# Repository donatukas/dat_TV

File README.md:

# dat_TV

* USB based modulator/demodulator with support for EN 300-744 DVB-T
transmission and reception.
* Powered from the USB bus, so no external power adapter is required
Full hardware modulation/demodulation, no host CPU computation required.
* Modulator (Transmitter):
Direct digital conversion to 50~950MHz and 1200~1350 MHz for excellent
signal quality
* UT-100A/UT-100B/UT-100C support configurable bandwidth from 2MHz to 8
MHz.

* Support only non-hierarchy mode
* Programmable digital attenuator
* Free Windows Stream Player
* Free Windows and Linux SDK

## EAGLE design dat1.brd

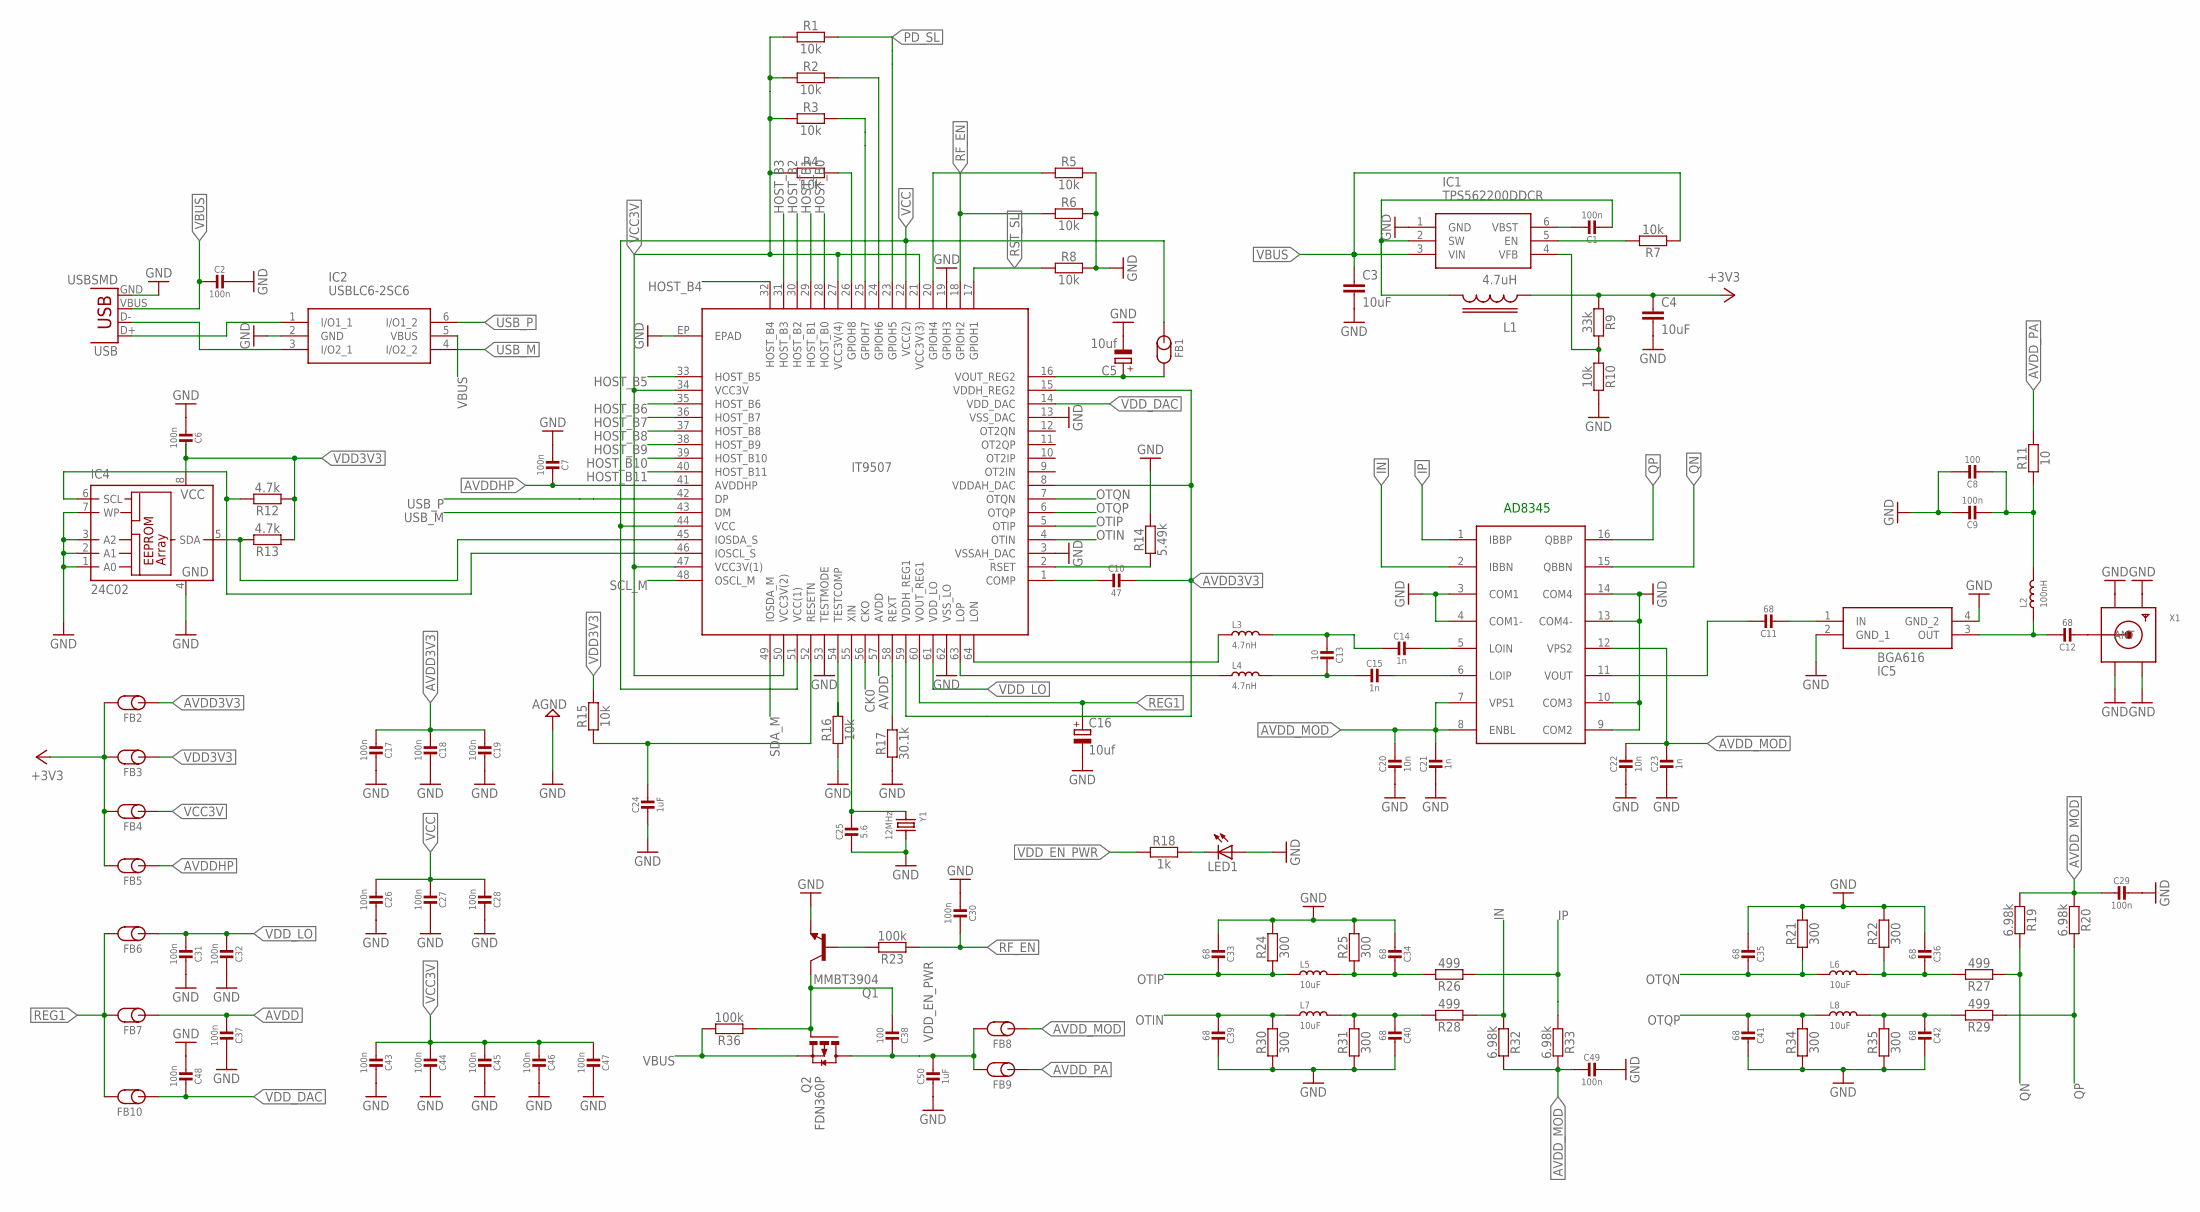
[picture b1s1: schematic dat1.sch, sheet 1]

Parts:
C1, C2, C6, C7, C9, C17, C18, C19, C26, C27, C28, C29, C30, C31, C32, C37, C43, C44, C45, C46, C47, C48, C49: 100n; _0402
C3, C4: 10uF; C0805K
C5, C16: 10uf; SMC_A
C8, C38: 100; _0402
C10: 47; _0402
C11, C12, C33, C34, C35, C36, C39, C40, C41, C42: 68; _0402
C13: 10; _0402
C14, C15, C21, C23: 1n; _0402
C20, C22: 10n; _0402
C24: 1uF; _0402
C25: 5.6; _0402
C50: 1uF; _0603
FB1, FB2, FB3, FB4, FB5, FB6, FB7, FB8, FB9, FB10: FB0603; INDC1608X95N
IC1: TPS562200DDCR; SOT95P280X110-6N
IC2: USBLC6-2SC6; SOT95P280X145-6N
IC3: CRYSTALVIDEO_IT9518; CRYSTALVIDEO_QFN64P40_IT9518
IC4: 24C02; SO-08
IC5: BGA616
IC6: AD8346; QSOP16
L1: 4.7uH; L_3X3
L2: 100nH; L0603@1
L3, L4: 4.7nH; L0603@1
L5, L6, L7, L8: 10uF; L0805@1
LED1: POWER; CHIPLED-0603-TTW
Q1: MMBT3904; SOT23-BEC
Q2: FDN360P; SUPER-SOT3
R1, R2, R3, R4, R5, R6, R7, R8, R10, R15, R16: 10k; C0402
R9: 33k; C0402
R11: 10; C0603
R12, R13: 4.7k; C0402
R14: 5.49k; C0402
R17: 30.1k; C0402
R18: 1k; C0402
R19, R20, R32, R33: 6.98k; C0402
R21, R22, R24, R25, R30, R31, R34, R35: 300; C0402
R23, R36: 100k; C0603
R26, R27, R28, R29: 499; C0402
USB: USBSMD; USB-MINIB
X1: MODULATOR_MICROBUILDER_SMACONNECTOR_EDGE_UFL; MODULATOR_MICROBUILDER_SMA_EDGELAUNCH_UFL
Y1: 12MHz; CRYSTAL_3.2X2.5

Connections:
+3V3: C4.1, FB2.2, FB3.2, FB4.2, FB5.2, L1.1, R9.1
AVDD: C37.2, FB7.1, IC3.57 (AVDD)
AVDD3V3: C10.1, C17.2, C18.2, C19.2, FB2.1, IC3.8 (VDDAH_DAC), IC3.15 (VDDH_REG2), IC3.59 (VDDH_REG1)
AVDDHP: C7.1, FB5.1, IC3.41 (AVDDHP)
AVDD_MOD: C20.1, C21.1, C22.1, C23.1, C29.2, C49.2, FB8.1, IC6.7 (VPS1), IC6.8 (ENBL), IC6.12 (VPS2), R19.1, R20.1, R32.2, R33.2
AVDD_PA: FB9.1, R11.2
CK0: IC3.56 (CKO); also elsewhere on the board
GND: C2.1, C3.2, C4.2, C5.-, C6.2, C7.2, C8.1, C9.1, C16.-, C17.1, C18.1, C19.1, C20.2, C21.2, C22.2, C23.2, C24.2, C25.1, C26.1, C27.1, C28.1, C29.1, C30.2, C31.1, C32.1, C33.2, C34.2, C35.2, C36.2, C37.1, C39.1, C40.1, C41.1, C42.1, C43.1, C44.1, C45.1, C46.1, C47.1, C48.2, C49.1, C50.2, IC1.1 (GND), IC2.2 (GND), IC3.3 (VSSAH_DAC), IC3.13 (VSS_DAC), IC3.19 (GPIOH3), IC3.53 (TESTMODE), IC3.62 (VSS_LO), IC3.EP (EPAD), IC4.1 (A0), IC4.2 (A1), IC4.3 (A2), IC4.4 (GND), IC4.7 (WP), IC5.2 (GND_1), IC5.4 (GND_2), IC6.3 (COM1), IC6.4 (COM1-), IC6.9 (COM2), IC6.10 (COM3), IC6.13 (COM4-), IC6.14 (COM4), LED1.A@1 (A), Q1.E, R5.2, R6.2, R8.2, R10.2, R14.2, R16.1, R17.1, R21.2, R22.2, R24.2, R25.2, R30.1, R31.1, R34.1, R35.1, USB.GND, X1.GND@1 (GND1), X1.GND@2 (GND2), X1.GND@3 (GND3), X1.GND@4 (GND4), Y1.2; also elsewhere on the board
HOST_B0: IC3.28 (HOST_B0); also elsewhere on the board
HOST_B1: IC3.29 (HOST_B1); also elsewhere on the board
HOST_B2: IC3.30 (HOST_B2); also elsewhere on the board
HOST_B3: IC3.31 (HOST_B3); also elsewhere on the board
HOST_B4: IC3.32 (HOST_B4); also elsewhere on the board
HOST_B5: IC3.33 (HOST_B5); also elsewhere on the board
HOST_B6: IC3.35 (HOST_B6); also elsewhere on the board
HOST_B7: IC3.36 (HOST_B7); also elsewhere on the board
HOST_B8: IC3.37 (HOST_B8); also elsewhere on the board
HOST_B9: IC3.38 (HOST_B9); also elsewhere on the board
HOST_B10: IC3.39 (HOST_B10); also elsewhere on the board
HOST_B11: IC3.40 (HOST_B11); also elsewhere on the board
IN: IC6.2 (IBBN), R28.1, R32.1
IP: IC6.1 (IBBP), R26.1, R33.1
unnamed: C1.2, IC1.2 (SW), L1.2
unnamed: C25.2, IC3.55 (XIN), Y1.1
unnamed: IC3.26 (GPIOH8), R4.2
unnamed: IC3.54 (TESTCOMP), R16.2
unnamed: C24.1, IC3.52 (RESETN), R15.1
unnamed: IC2.3 (I/O2_1), USB.D-
unnamed: C1.1, IC1.6 (VBST)
unnamed: C5.+, FB1.2, IC3.16 (VOUT_REG2)
unnamed: IC3.58 (REXT), R17.2
unnamed: IC3.45 (IOSDA_S), IC4.5 (SDA), R13.2
unnamed: IC3.46 (IOSCL_S), IC4.6 (SCL), R12.2
unnamed: IC3.64 (LON), L3.1
unnamed: IC3.63 (LOP), L4.1
unnamed: IC1.5 (EN), R7.2
unnamed: C12.2, X1.P (ANT)
unnamed: C8.2, C9.2, L2.2, R11.1
unnamed: C15.1, IC6.6 (LOIP)
unnamed: LED1.C@1 (C), R18.2
unnamed: C11.1, IC6.11 (VOUT)
unnamed: IC2.1 (I/O1_1), USB.D+
unnamed: IC1.4 (VFB), R9.2, R10.1
unnamed: C14.1, IC6.5 (LOIN)
unnamed: C13.1, C15.2, L4.2
unnamed: C13.2, C14.2, L3.2
unnamed: C36.1, L6.2, R22.1, R27.2
unnamed: C42.2, L8.2, R29.2, R35.2
unnamed: C34.1, L5.2, R25.1, R26.2
unnamed: C40.2, L7.2, R28.2, R31.2
unnamed: IC3.25 (GPIOH7), R3.2
unnamed: IC3.24 (GPIOH6), R2.2
unnamed: C10.2, IC3.1 (COMP)
unnamed: IC3.2 (RSET), R14.1
unnamed: C12.1, IC5.3 (OUT), L2.1
unnamed: C11.2, IC5.1 (IN)
unnamed: IC3.20 (GPIOH4), R5.1
OTIN: C39.2, IC3.4 (OTIN), L7.1, R30.2
OTIP: C33.1, IC3.5 (OTIP), L5.1, R24.1
OTQN: C35.1, IC3.7 (OTQN), L6.1, R21.1
OTQP: C41.2, IC3.6 (OTQP), L8.1, R34.2
PD_SL: IC3.23 (GPIOH5), R1.2; also elsewhere on the board
Q1: Q1.B, R23.2
QN: IC6.15 (QBBN), R19.2, R27.1
QP: IC6.16 (QBBP), R20.2, R29.1
REG1: C16.+, FB6.2, FB7.2, FB10.2, IC3.60 (VOUT_REG1)
RF_EN: C30.1, IC3.18 (GPIOH2), R6.1, R23.1
RST_SL: IC3.17 (GPIOH1), R8.1; also elsewhere on the board
SCL_M: IC3.48 (OSCL_M); also elsewhere on the board
SDA_M: IC3.49 (IOSDA_M); also elsewhere on the board
USB_M: IC2.4 (I/O2_2), IC3.43 (DM)
USB_P: IC2.6 (I/O1_2), IC3.42 (DP)
V: C38.2, Q1.C, Q2.1 (G), R36.1
VBUS: C2.2, C3.1, IC1.3 (VIN), IC2.5 (VBUS), Q2.2 (S), R7.1, R36.2, USB.VBUS; also elsewhere on the board
VCC: C26.2, C27.2, C28.2, FB1.1, IC3.22 (VCC(2)), IC3.44 (VCC), IC3.51 (VCC(1))
VCC3V: C43.2, C44.2, C45.2, C46.2, C47.2, FB4.1, IC3.21 (VCC3V(3)), IC3.27 (VCC3V(4)), IC3.34 (VCC3V), IC3.47 (VCC3V(1)), IC3.50 (VCC3V(2)), R1.1, R2.1, R3.1, R4.1
VDD3V3: C6.1, FB3.1, IC4.8 (VCC), R12.1, R13.1, R15.2
VDD_DAC: C48.1, FB10.1, IC3.14 (VDD_DAC)
VDD_EN_PWR: C38.1, C50.1, FB8.2, FB9.2, Q2.3 (D), R18.1
VDD_LO: C31.2, C32.2, FB6.1, IC3.61 (VDD_LO)

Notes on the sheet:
AD8345

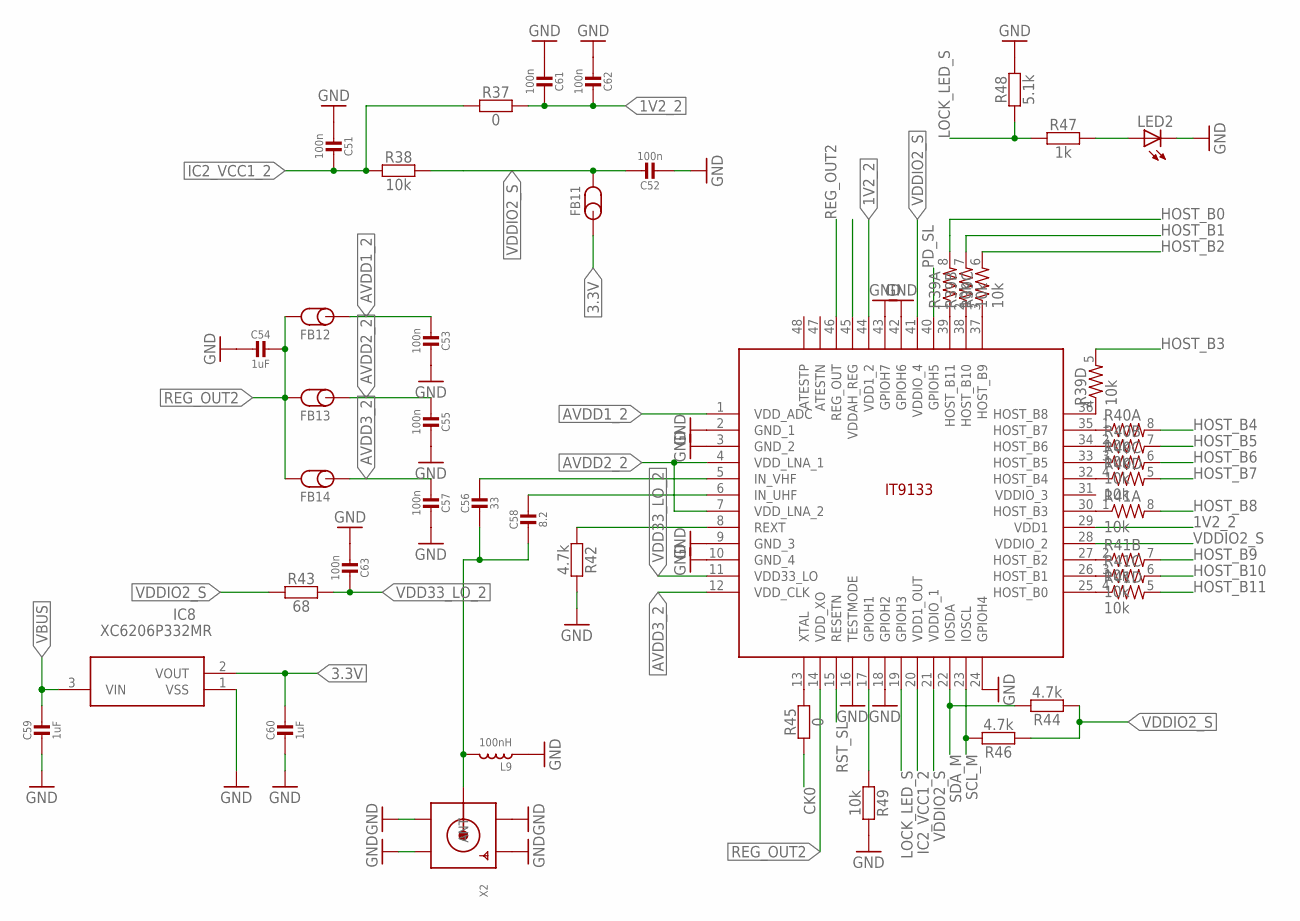
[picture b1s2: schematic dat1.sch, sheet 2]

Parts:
C51, C52, C53, C55, C57, C61, C62, C63: 100n; _0402
C54: 1uF; _0402
C56: 33; _0402
C58: 8.2; _0402
C59, C60: 1uF; _0603
FB11, FB12, FB13, FB14: FB0603; INDC1608X95N
IC7: CRYSTALVIDEO_IT9133; CRYSTALVIDEO_QFN48P50_IT9133
IC8: XC6206P332MR; SOT95P280X130-3N
L9: 100nH; L0603S
LED2: POWER; CHIPLED-0603-TTW
R37, R45: 0; C0402
R38, R49: 10k; C0402
R39, R40, R41: 10k; 0603-ARV
R42, R44, R46: 4.7k; C0402
R43: 68; C0402
R47: 1k; C0402
R48: 5.1k; C0402
X2: MODULATOR_MICROBUILDER_SMACONNECTOR_EDGE_UFL; MODULATOR_MICROBUILDER_SMA_EDGELAUNCH_UFL

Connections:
1V2_2: C61.1, C62.1, IC7.29 (VDD1), IC7.44 (VDD1_2), R37.2
3.3V: C60.1, FB11.1, IC8.2 (VOUT)
AVDD1_2: C53.2, FB12.1, IC7.1 (VDD_ADC)
AVDD2_2: C55.2, FB13.1, IC7.4 (VDD_LNA_1), IC7.7 (VDD_LNA_2)
AVDD3_2: C57.2, FB14.1, IC7.12 (VDD_CLK)
CK0: R45.1; also elsewhere on the board
GND: C51.2, C52.2, C53.1, C54.2, C55.1, C57.1, C59.2, C60.2, C61.2, C62.2, C63.2, IC7.2 (GND_1), IC7.3 (GND_2), IC7.9 (GND_3), IC7.10 (GND_4), IC7.16 (TESTMODE), IC7.18 (GPIOH2), IC7.24 (GPIOH4), IC7.42 (GPIOH6), IC7.43 (GPIOH7), IC8.1 (VSS), L9.1, LED2.C@1 (C), R42.2, R48.2, R49.2, X2.GND@1 (GND1), X2.GND@2 (GND2), X2.GND@3 (GND3), X2.GND@4 (GND4); also elsewhere on the board
HOST_B0: R39.8 (2); also elsewhere on the board
HOST_B1: R39.7 (2); also elsewhere on the board
HOST_B2: R39.6 (2); also elsewhere on the board
HOST_B3: R39.5 (2); also elsewhere on the board
HOST_B4: R40.8 (2); also elsewhere on the board
HOST_B5: R40.7 (2); also elsewhere on the board
HOST_B6: R40.6 (2); also elsewhere on the board
HOST_B7: R40.5 (2); also elsewhere on the board
HOST_B8: R41.8 (2); also elsewhere on the board
HOST_B9: R41.7 (2); also elsewhere on the board
HOST_B10: R41.6 (2); also elsewhere on the board
HOST_B11: R41.5 (2); also elsewhere on the board
IC2_VCC1_2: C51.1, IC7.20 (VDD1_OUT), R37.1, R38.1
LOCK_LED_S: IC7.19 (GPIOH3), R47.1, R48.1
unnamed: IC7.13 (XTAL), R45.2
unnamed: C56.2, C58.2, L9.2, X2.P (ANT)
unnamed: IC7.39 (HOST_B11), R39.1
unnamed: IC7.38 (HOST_B10), R39.2 (1)
unnamed: IC7.37 (HOST_B9), R39.3 (1)
unnamed: IC7.36 (HOST_B8), R39.4 (1)
unnamed: IC7.35 (HOST_B7), R40.1
unnamed: IC7.34 (HOST_B6), R40.2 (1)
unnamed: IC7.33 (HOST_B5), R40.3 (1)
unnamed: IC7.32 (HOST_B4), R40.4 (1)
unnamed: IC7.30 (HOST_B3), R41.1
unnamed: IC7.27 (HOST_B2), R41.2 (1)
unnamed: IC7.26 (HOST_B1), R41.3 (1)
unnamed: IC7.25 (HOST_B0), R41.4 (1)
unnamed: IC7.17 (GPIOH1), R49.1
unnamed: C56.1, IC7.5 (IN_VHF)
unnamed: C58.1, IC7.6 (IN_UHF)
unnamed: IC7.8 (REXT), R42.1
unnamed: LED2.A@1 (A), R47.2
PD_SL: IC7.40 (GPIOH5); also elsewhere on the board
REG_OUT2: C54.1, FB12.2, FB13.2, FB14.2, IC7.14 (VDD_XO), IC7.46 (REG_OUT)
RST_SL: IC7.15 (RESETN); also elsewhere on the board
SCL_M: IC7.23 (IOSCL), R46.2; also elsewhere on the board
SDA_M: IC7.22 (IOSDA), R44.2; also elsewhere on the board
VBUS: C59.1, IC8.3 (VIN); also elsewhere on the board
VDD33_LO_2: C63.1, IC7.11 (VDD33_LO), R43.2
VDDIO2_S: C52.1, FB11.2, IC7.21 (VDDIO_1), IC7.28 (VDDIO_2), IC7.41 (VDDIO_4), R38.2, R43.1, R44.1, R46.1

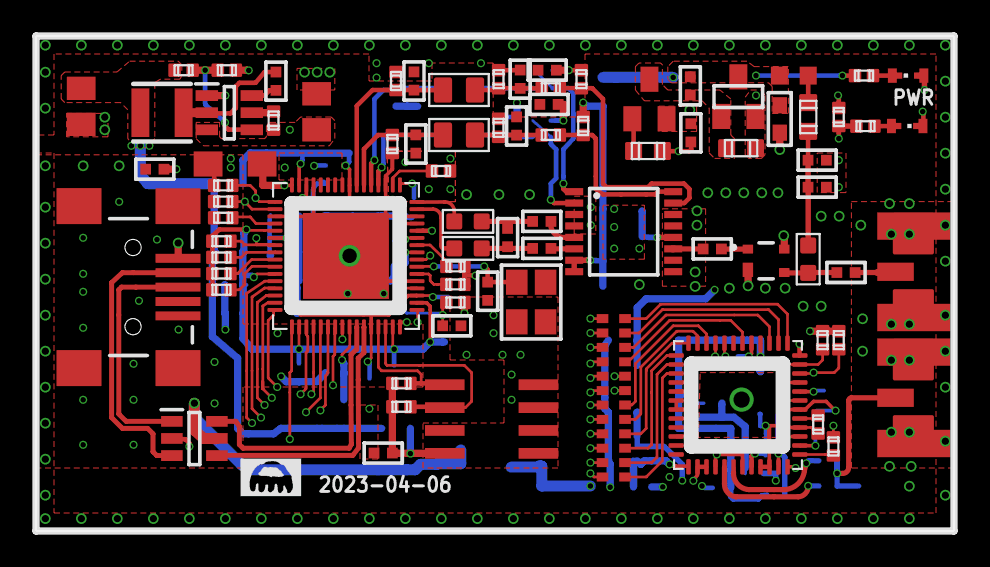
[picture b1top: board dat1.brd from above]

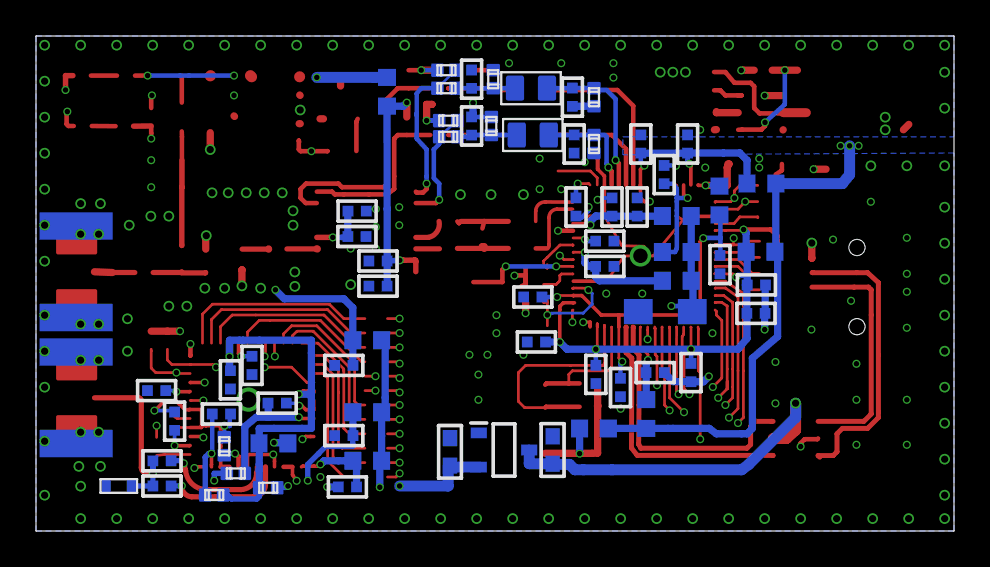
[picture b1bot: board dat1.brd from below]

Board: 4 copper layers, 51.0 x 27.5 mm, 151 parts (68 on the bottom side), 109 nets.

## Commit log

2024-02-07 datv
    datv

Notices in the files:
parts and their libraries:
SparkFun-Connectors: Licensing: Creative Commons ShareAlike 4.0 International - https://creativecommons.org/licenses/by-sa/4.0
microbuilder: This work is placed in the public domain, and may be freely used for commercial and non-commercial work with the following conditions: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
